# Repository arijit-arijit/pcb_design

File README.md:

# pcb_design
my journey of learning PCB design from scratch through tutorials and projects

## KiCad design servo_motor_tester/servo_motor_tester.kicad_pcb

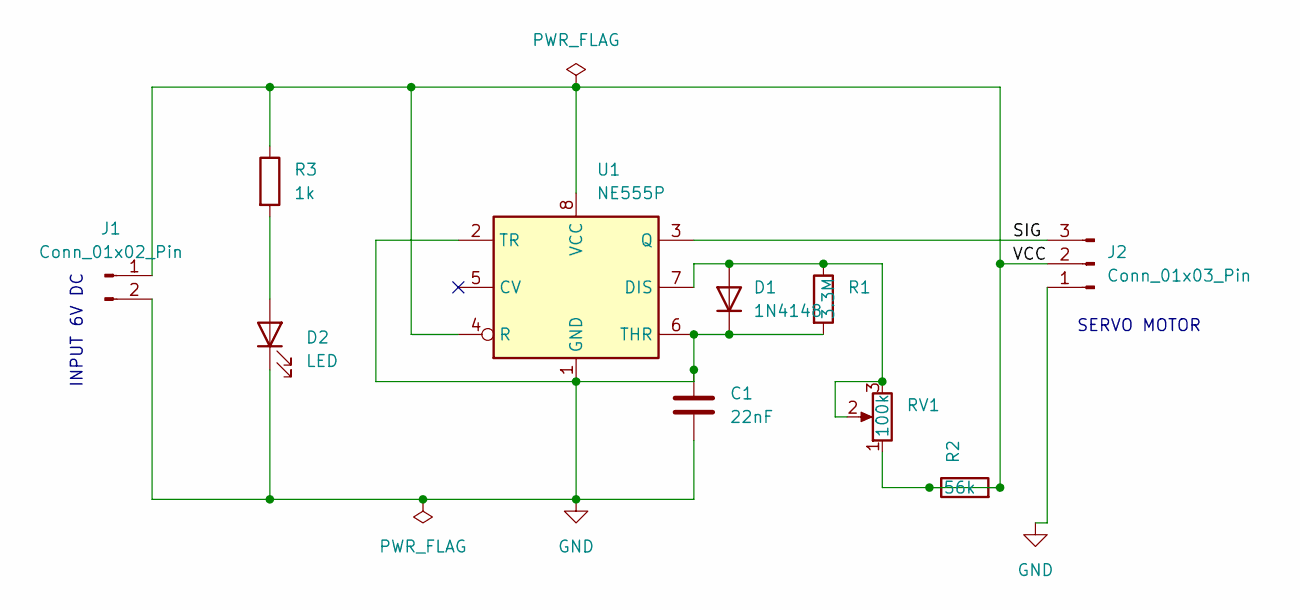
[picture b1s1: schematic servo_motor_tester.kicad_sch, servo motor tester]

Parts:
C1: 22nF; C_Disc_D4.3mm_W1.9mm_P5.00mm
D1: 1N4148; D_DO-35_SOD27_P7.62mm_Horizontal
D2: LED; LED_D3.0mm
J1: Conn_01x02_Pin; PinHeader_1x02_P2.54mm_Horizontal
J2: Conn_01x03_Pin; PinHeader_1x03_P2.54mm_Horizontal
R1: 3.3M; R_Axial_DIN0204_L3.6mm_D1.6mm_P7.62mm_Horizontal
R2: 56k; R_Axial_DIN0204_L3.6mm_D1.6mm_P7.62mm_Horizontal
R3: 1k; R_Axial_DIN0204_L3.6mm_D1.6mm_P7.62mm_Horizontal
RV1: 100k; Potentiometer_Alps_RK163_Single_Horizontal
U1: NE555P; DIP-8_W7.62mm

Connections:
/SIG: J2.3, U1.3 (Q)
/VCC: J1.1, J2.2, R2.1, R2.2, R3.1, RV1.1, U1.4 (R), U1.8 (VCC)
GND: C1.1, C1.2, D1.1 (K), D2.1 (K), J1.2, J2.1, R1.2, U1.1 (GND), U1.2 (TR), U1.6 (THR)
unnamed: D1.2 (A), R1.1, RV1.2, RV1.3, U1.7 (DIS)
unnamed: D2.2 (A), R3.2

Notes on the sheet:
INPUT 6V DC
SERVO MOTOR

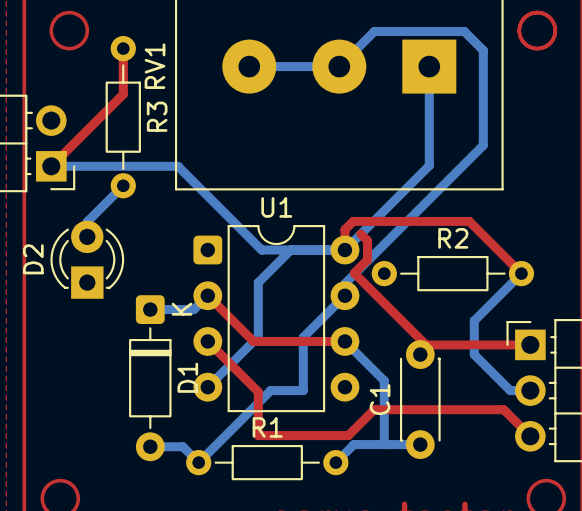
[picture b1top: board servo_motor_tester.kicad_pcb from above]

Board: 2 copper layers, 10 parts (0 on the bottom side), 5 nets.

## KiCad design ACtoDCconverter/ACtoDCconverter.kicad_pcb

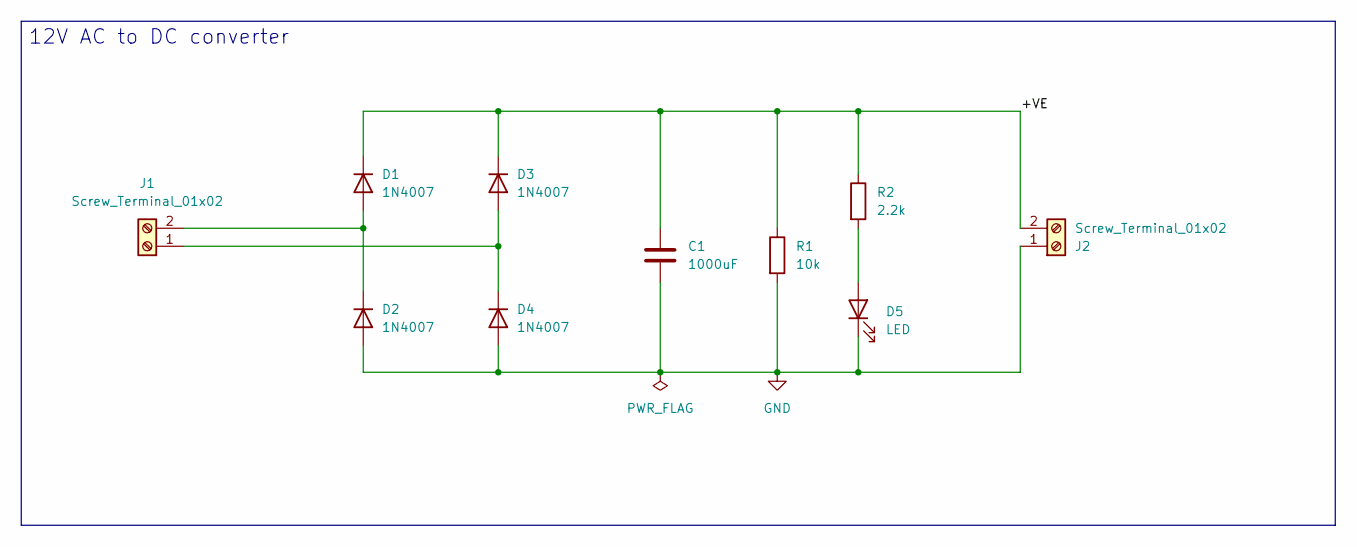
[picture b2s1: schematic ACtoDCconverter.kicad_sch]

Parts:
C1: 1000uF; C_Radial_D8.0mm_H11.5mm_P3.50mm
D1, D2, D3, D4: 1N4007; D_DO-41_SOD81_P10.16mm_Horizontal
D5: LED; LED_D5.0mm
J1, J2: Screw_Terminal_01x02; TerminalBlock_Phoenix_MKDS-1,5-2-5.08_1x02_P5.08mm_Horizont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
R1: 10k; R_Axial_DIN0204_L3.6mm_D1.6mm_P7.62mm_Horizontal
R2: 2.2k; R_Axial_DIN0204_L3.6mm_D1.6mm_P7.62mm_Horizontal

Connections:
/+VE: C1.1, D1.1 (K), D3.1 (K), J2.2, R1.1, R2.1
GND: C1.2, D2.2 (A), D4.2 (A), D5.1 (K), J2.1, R1.2
unnamed: D1.2 (A), D2.1 (K), J1.2
unnamed: D3.2 (A), D4.1 (K), J1.1
unnamed: D5.2 (A), R2.2

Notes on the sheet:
12V AC to DC converter

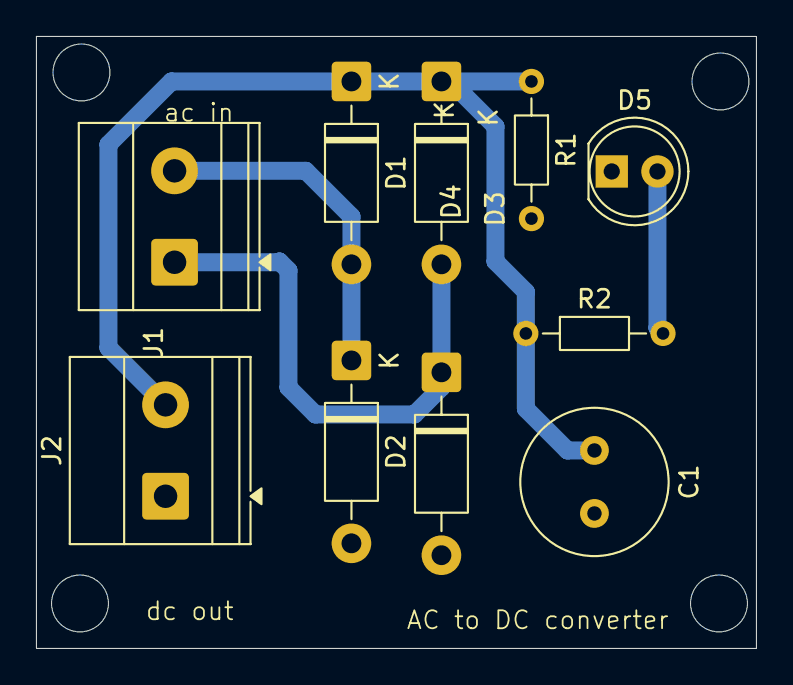
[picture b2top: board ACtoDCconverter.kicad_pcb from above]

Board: 2 copper layers, 40.0 x 34.0 mm, 10 parts (0 on the bottom side), 5 nets.

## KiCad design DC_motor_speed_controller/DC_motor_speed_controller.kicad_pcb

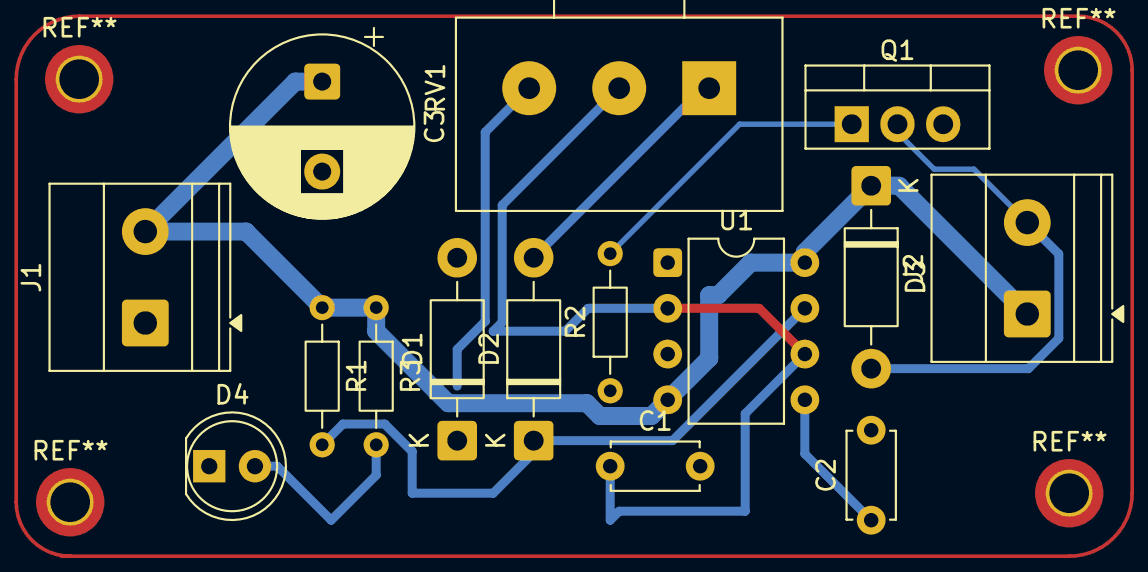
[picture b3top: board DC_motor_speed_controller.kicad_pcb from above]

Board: 2 copper layers, 15 parts (0 on the bottom side), 11 nets.

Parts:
C1, C2: 100nF; C_Disc_D4.7mm_W2.5mm_P5.00mm
C3: 1000nF; CP_Radial_D10.0mm_P5.00mm
D1, D2, D3: 1N4007; D_DO-41_SOD81_P10.16mm_Horizontal
D4: LED; LED_D5.0mm
J1, J2: Screw_Terminal_01x02; TerminalBlock_Phoenix_MKDS-1,5-2-5.08_1x02_P5.08mm_Horizont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
Q1: TIP122; TO-220-3_Vertical
R1, R2: 1k; R_Axial_DIN0204_L3.6mm_D1.6mm_P7.62mm_Horizontal
R3: 2.2k; R_Axial_DIN0204_L3.6mm_D1.6mm_P7.62mm_Horizontal
RV1: 100k; Potentiometer_Alps_RK163_Single_Horizontal
U1: NE555P; DIP-8_W7.62mm

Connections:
GND: C1.2, C2.2, C3.2, D4.1 (K), J1.1, Q1.3 (E), U1.1 (GND)
unnamed: D1.2 (A), D2.1 (K), R1.2, U1.7 (DIS)
unnamed: D1.1 (K), RV1.3
unnamed: D2.2 (A), RV1.1
unnamed: D3.2 (A), J2.2, Q1.2 (C)
unnamed: C3.1, D3.1 (K), J1.2, J2.1, R1.1, R3.1, U1.4 (R), U1.8 (VCC)
unnamed: D4.2 (A), R3.2
unnamed: Q1.1 (B), R2.2
unnamed: C2.1, U1.5 (CV)
unnamed: R2.1, U1.3 (Q)
unnamed: C1.1, RV1.2, U1.2 (TR), U1.6 (THR)

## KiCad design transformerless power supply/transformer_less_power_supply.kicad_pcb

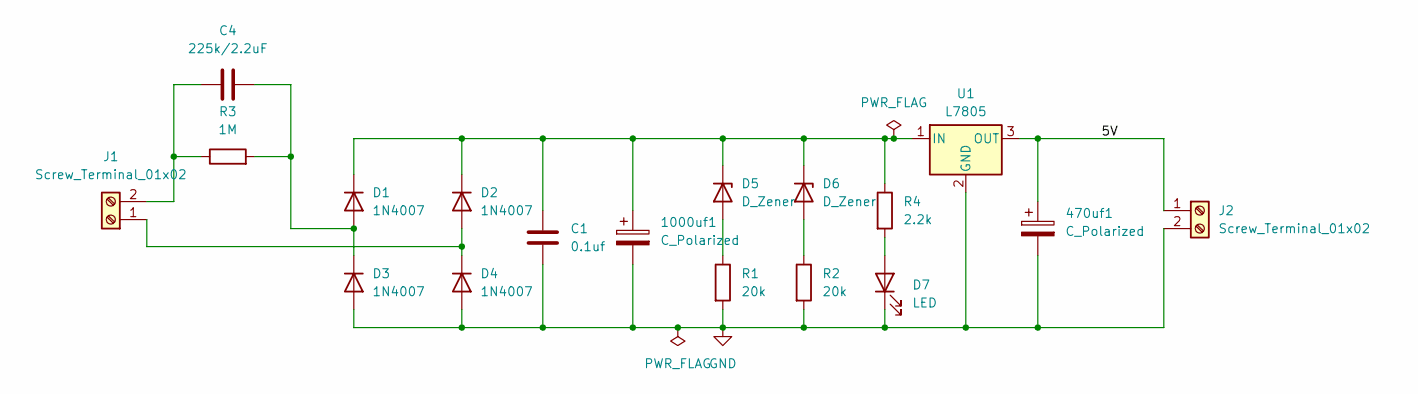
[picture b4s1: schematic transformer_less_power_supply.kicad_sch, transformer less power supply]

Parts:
470uf1: C_Polarized; CP_Radial_D10.0mm_P3.80mm
1000uf1: C_Polarized; CP_Radial_D10.0mm_P5.00mm
C1: 0.1uf; C_Disc_D4.7mm_W2.5mm_P5.00mm
C4: 225k/2.2uF; C_Rect_L18.0mm_W6.0mm_P15.00mm_FKS3_FKP3
D1, D2, D3, D4: 1N4007; D_DO-41_SOD81_P10.16mm_Horizontal
D5, D6: D_Zener; D_A-405_P7.62mm_Horizontal
D7: LED; LED_D5.0mm
J1, J2: Screw_Terminal_01x02; TerminalBlock_Phoenix_PT-1,5-2-5.0-H_1x02_P5.00mm_Horizontal
R1, R2: 20k; R_Axial_DIN0207_L6.3mm_D2.5mm_P7.62mm_Horizontal
R3: 1M; R_Axial_DIN0207_L6.3mm_D2.5mm_P7.62mm_Horizontal
R4: 2.2k; R_Axial_DIN0207_L6.3mm_D2.5mm_P7.62mm_Horizontal
U1: L7805; TO-220-3_Vertical

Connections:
/5V: 470uf1.1, J2.1, U1.3 (OUT)
GND: 470uf1.2, 1000uf1.2, C1.2, D3.2 (A), D4.2 (A), D7.1 (K), J2.2, R1.2, R2.2, U1.2 (GND)
unnamed: C4.2, D1.2 (A), D3.1 (K), R3.2
unnamed: 1000uf1.1, C1.1, D1.1 (K), D2.1 (K), D5.1 (K), D6.1 (K), R4.1, U1.1 (IN)
unnamed: D2.2 (A), D4.1 (K), J1.1
unnamed: D5.2 (A), R1.1
unnamed: D6.2 (A), R2.1
unnamed: D7.2 (A), R4.2
unnamed: C4.1, J1.2, R3.1

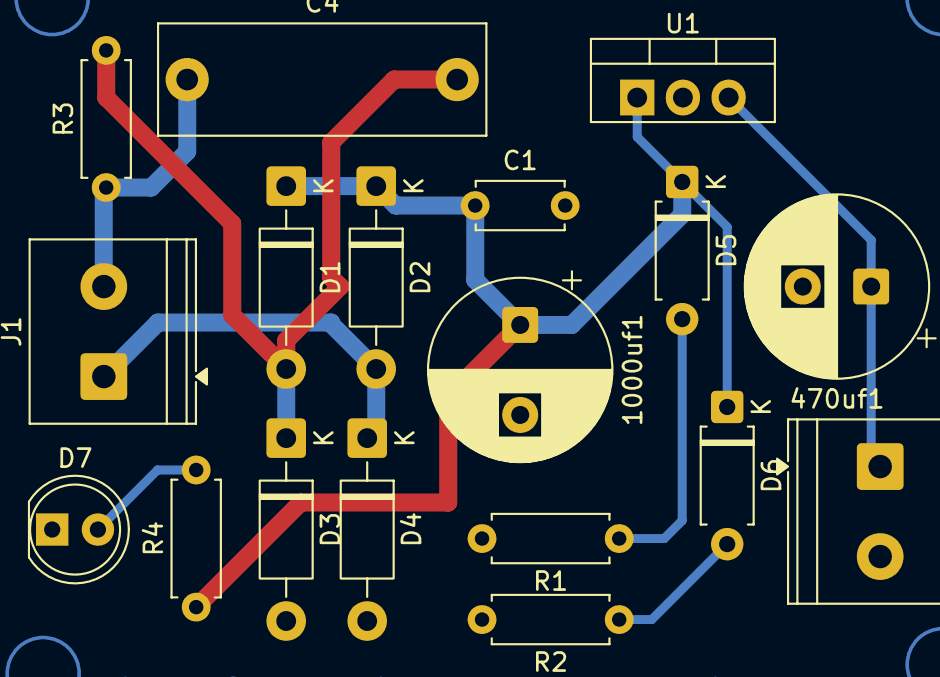
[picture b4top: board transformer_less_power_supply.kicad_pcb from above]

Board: 2 copper layers, 18 parts (0 on the bottom side), 9 nets.

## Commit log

2025-12-19 Create transformer_less_power_supply
2025-12-19 Create transformer less power supply
